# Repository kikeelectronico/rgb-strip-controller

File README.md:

View this project on [CADLAB.io](https://cadlab.io/project/24089). 

# RGB Strip controller

***

<br /><span xmlns:dct="http://purl.org/dc/terms/" property="dct:title">RGB strip controller</span> by <span xmlns:cc="http://creativecommons.org/ns#" property="cc:attributionName">Enrique Gómez</span> licensed by <a rel="license" href="http://creativecommons.org/licenses/by-sa/4.0/">Creative Commons Attribution-ShareAlike 4.0 International License</a>.<br /><br />

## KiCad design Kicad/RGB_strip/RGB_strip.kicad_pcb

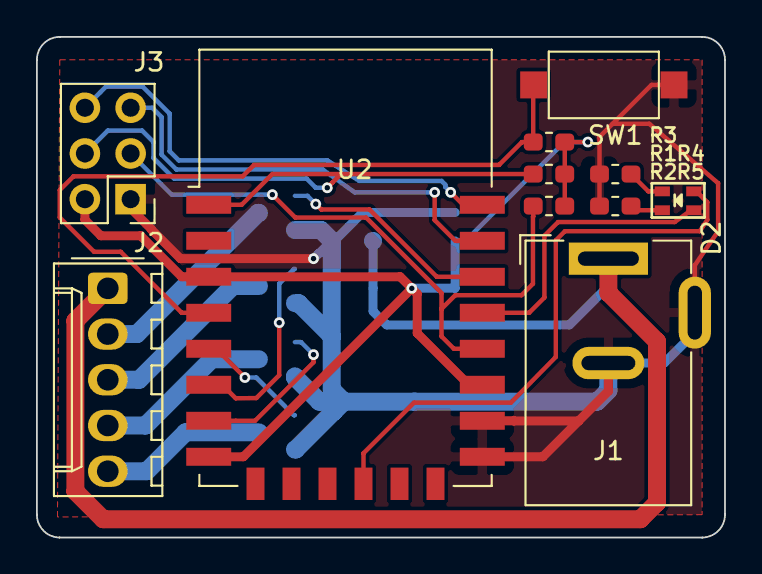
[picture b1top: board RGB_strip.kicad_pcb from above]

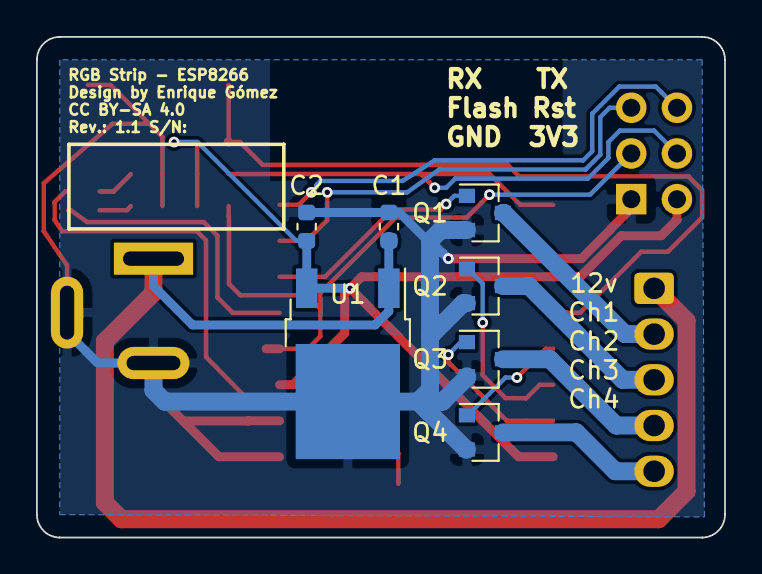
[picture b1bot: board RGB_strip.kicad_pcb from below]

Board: 2 copper layers, 38.2 x 27.8 mm, 18 parts (7 on the bottom side), 20 nets.

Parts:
C1, C2: 330nF; C_0603_1608Metric
D2: TJ-S1615SW6TGLCBG-A5
J1: Barrel_Jack_Switch; BarrelJack_Wuerth_6941xx301002
J2: LED; Molex_KK-254_AE-6410-05A_1x05_P2.54mm_Vertical
J3: Conn_01x06_Female; PinHeader_2x03_P2.54mm_Vertical
Q1, Q2, Q3, Q4: AO3420; SOT-23
R1, R2, R3: 10k; R_0603_1608Metric_Pad1.05x0.95mm_HandSolder
R4, R5: 19R1; R_0603_1608Metric_Pad1.05x0.95mm_HandSolder
SW1: 1TS002E-2500-2500-CT; SW_SPST_CK_RS282G05A3
U1: MC33275DT-3.3RKG; TO-252-2
U2: ESP-12E

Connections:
+3V3: C2.1, J3.2, R1.1, R2.1, R3.1, U1.3, U2.3, U2.8, U2.17
+12V: C1.1, J1.1, J2.1, U1.1
/Flash: J3.3, R2.2, U2.18
/RX: J3.5, U2.21
/Rst: J3.4, R1.2, U2.1
/TX: J3.6, U2.22
/blue_c: Q3.1, U2.7
/green_c: Q2.1, U2.6
/green_led: D2.1, U2.12
/red_c: Q1.1, U2.20
/white_c: Q4.1, U2.5
GND: C1.2, C2.2, J1.2, J1.3, J3.1, Q1.2, Q2.2, Q3.2, Q4.2, R4.1, R5.1, SW1.2, U1.2, U2.15, U2.16
unnamed: D2.2, R4.2
unnamed: D2.3, U2.19
unnamed: D2.4, R5.2
unnamed: J2.2, Q1.3
unnamed: J2.3, Q2.3
unnamed: J2.4, Q3.3
unnamed: J2.5, Q4.3
unnamed: R3.2, SW1.1, U2.4

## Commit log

2021-03-26 kick off
2021-03-26 readme
2021-03-26 license
2021-03-26 Backlink to CADLAB.io has been added.
2021-03-27 add labels
2021-03-27 update gerbers
2021-03-27 readme version

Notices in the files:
Kicad/RGB_strip/RGB_strip.kicad_pcb:
CC BY-SA 4.0
